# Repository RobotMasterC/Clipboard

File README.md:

# Clipboard
A TKL Keyboard that has expansion slots on both sides for extras

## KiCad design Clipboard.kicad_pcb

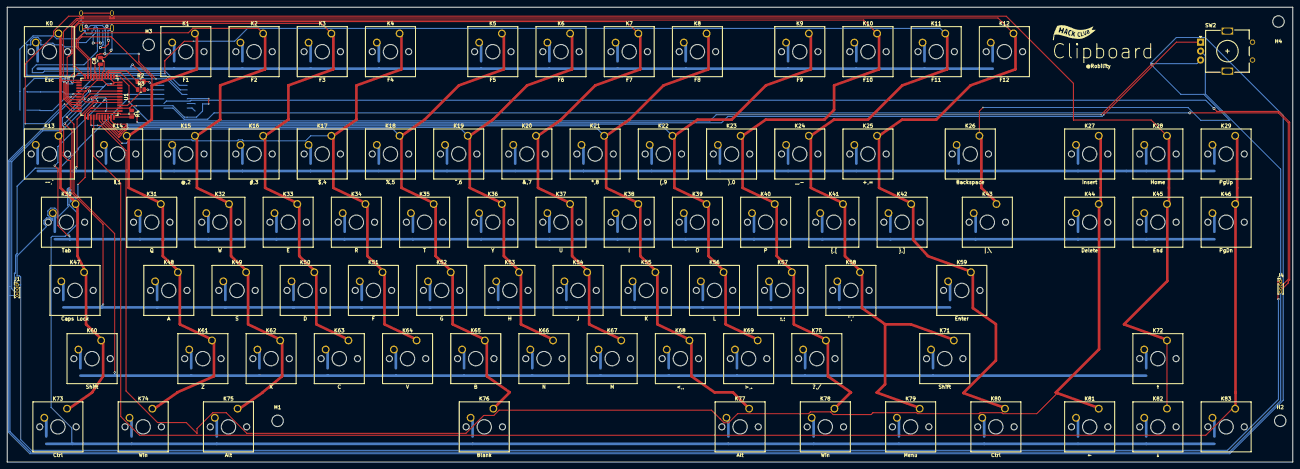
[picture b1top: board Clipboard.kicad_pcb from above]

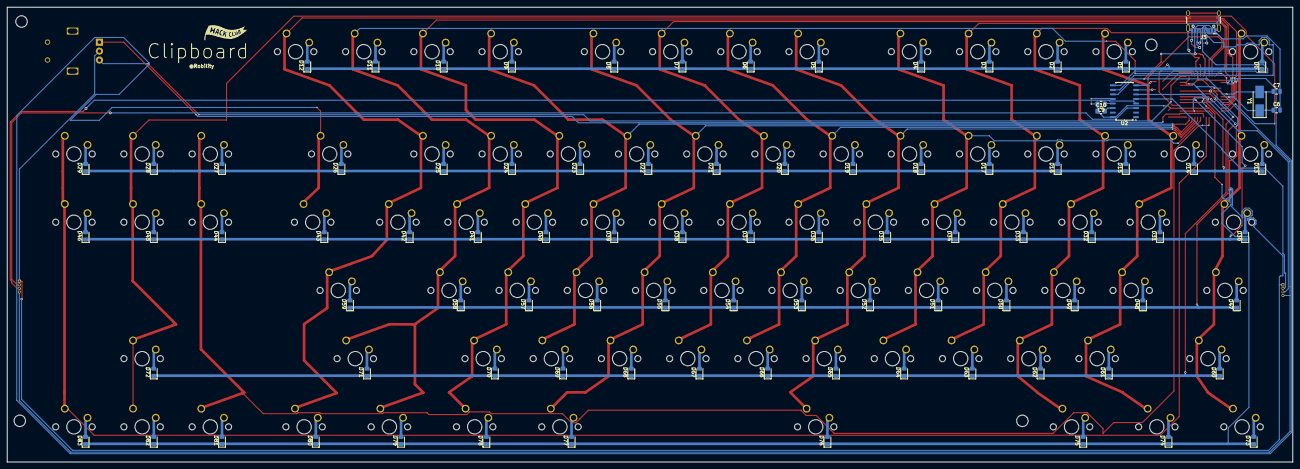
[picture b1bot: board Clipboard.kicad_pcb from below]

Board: 2 copper layers, 359.0 x 127.0 mm, 187 parts (91 on the bottom side), 128 nets.

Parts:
C6, C7: 22p; C_0805_2012Metric
C8: 1u; C_0805_2012Metric
C9, C10: 10uF; C_0805_2012Metric_Pad1.18x1.45mm_HandSolder
D0, D1, D2, D3, D4, D5, D6, D7, D8, D9, D10, D11, D12, D13, D14, D15, D16, D17, D18, D19, D20, D21, D22, D23, D24, D25, D26, D27, D28, D29, D30, D31, D32, D33, D34, D35, D36, D37, D38, D39, D40, D41, D42, D43, D44, D45, D46, D47, D48, D49, D50, D51, D52, D53, D54, D55, D56, D57, D58, D59, D60, D61, D62, D63, D64, D65, D66, D67, D68, D69, D70, D71, D72, D73, D74, D75, D76, D77, D78, D79, D80, D81, D82, D83: D; D_0805_2012Metric_Pad1.15x1.40mm_HandSolder
H1, H2, H3, H4: MountingHole; MountingHole_3.2mm_M3_DIN965
J1, J4: Conn_01x04_Socket; PinHeader_1x04_P1.00mm_Vertical
J3: USB_C_Receptacle_USB2.0_16P; USB_C_Receptacle_HCTL_HC-TYPE-C-16P-01A
K0: Esc; SW_Cherry_MX_1.00u_PCB
K1: F1; SW_Cherry_MX_1.00u_PCB
K2: F2; SW_Cherry_MX_1.00u_PCB
K3: F3; SW_Cherry_MX_1.00u_PCB
K4: F4; SW_Cherry_MX_1.00u_PCB
K5: F5; SW_Cherry_MX_1.00u_PCB
K6: F6; SW_Cherry_MX_1.00u_PCB
K7: F7; SW_Cherry_MX_1.00u_PCB
K8: F8; SW_Cherry_MX_1.00u_PCB
K9: F9; SW_Cherry_MX_1.00u_PCB
K10: F10; SW_Cherry_MX_1.00u_PCB
K11: F11; SW_Cherry_MX_1.00u_PCB
K12: F12; SW_Cherry_MX_1.00u_PCB
K13: ~~,`; SW_Cherry_MX_1.00u_PCB
K14: !,1; SW_Cherry_MX_1.00u_PCB
K15: @,2; SW_Cherry_MX_1.00u_PCB
K16: #,3; SW_Cherry_MX_1.00u_PCB
K17: $,4; SW_Cherry_MX_1.00u_PCB
K18: %,5; SW_Cherry_MX_1.00u_PCB
K19: ^,6; SW_Cherry_MX_1.00u_PCB
K20: &,7; SW_Cherry_MX_1.00u_PCB
K21: *,8; SW_Cherry_MX_1.00u_PCB
K22: (,9; SW_Cherry_MX_1.00u_PCB
K23: ),0; SW_Cherry_MX_1.00u_PCB
K24: _,-; SW_Cherry_MX_1.00u_PCB
K25: +,=; SW_Cherry_MX_1.00u_PCB
K26: Backspace; SW_Cherry_MX_2.00u_PCB
K27: Insert; SW_Cherry_MX_1.00u_PCB
K28: Home; SW_Cherry_MX_1.00u_PCB
K29: PgUp; SW_Cherry_MX_1.00u_PCB
K30: Tab; SW_Cherry_MX_1.50u_PCB
K31: Q; SW_Cherry_MX_1.00u_PCB
K32: W; SW_Cherry_MX_1.00u_PCB
K33: E; SW_Cherry_MX_1.00u_PCB
K34: R; SW_Cherry_MX_1.00u_PCB
K35: T; SW_Cherry_MX_1.00u_PCB
K36: Y; SW_Cherry_MX_1.00u_PCB
K37: U; SW_Cherry_MX_1.00u_PCB
K38: I; SW_Cherry_MX_1.00u_PCB
K39: O; SW_Cherry_MX_1.00u_PCB
K40: P; SW_Cherry_MX_1.00u_PCB
K41: {,[; SW_Cherry_MX_1.00u_PCB
K42: },]; SW_Cherry_MX_1.00u_PCB
K43: |,\; SW_Cherry_MX_1.50u_PCB
K44: Delete; SW_Cherry_MX_1.00u_PCB
K45: End; SW_Cherry_MX_1.00u_PCB
K46: PgDn; SW_Cherry_MX_1.00u_PCB
K47: Caps Lock; SW_Cherry_MX_1.75u_PCB
K48: A; SW_Cherry_MX_1.00u_PCB
K49: S; SW_Cherry_MX_1.00u_PCB
K50: D; SW_Cherry_MX_1.00u_PCB
K51: F; SW_Cherry_MX_1.00u_PCB
K52: G; SW_Cherry_MX_1.00u_PCB
K53: H; SW_Cherry_MX_1.00u_PCB
K54: J; SW_Cherry_MX_1.00u_PCB
K55: K; SW_Cherry_MX_1.00u_PCB
K56: L; SW_Cherry_MX_1.00u_PCB
K57: :,;; SW_Cherry_MX_1.00u_PCB
K58: ",'; SW_Cherry_MX_1.00u_PCB
K59: Enter; SW_Cherry_MX_2.25u_PCB
K60: Shift; SW_Cherry_MX_2.25u_PCB
K61: Z; SW_Cherry_MX_1.00u_PCB
K62: X; SW_Cherry_MX_1.00u_PCB
K63: C; SW_Cherry_MX_1.00u_PCB
K64: V; SW_Cherry_MX_1.00u_PCB
K65: B; SW_Cherry_MX_1.00u_PCB
K66: N; SW_Cherry_MX_1.00u_PCB
K67: M; SW_Cherry_MX_1.00u_PCB
K68: <,,; SW_Cherry_MX_1.00u_PCB
K69: >,.; SW_Cherry_MX_1.00u_PCB
K70: ?,/; SW_Cherry_MX_1.00u_PCB
K71: Shift; SW_Cherry_MX_2.75u_PCB
K72: ↑; SW_Cherry_MX_1.00u_PCB
K73, K80: Ctrl; SW_Cherry_MX_1.25u_PCB
K74, K78: Win; SW_Cherry_MX_1.25u_PCB
K75, K77: Alt; SW_Cherry_MX_1.25u_PCB
K76: Blank; SW_Cherry_MX_6.25u_PCB
K79: Menu; SW_Cherry_MX_1.25u_PCB
K81: ←; SW_Cherry_MX_1.00u_PCB
K82: ↓; SW_Cherry_MX_1.00u_PCB
K83: →; SW_Cherry_MX_1.00u_PCB
R2, R3: 22R; R_0805_2012Metric
R4: 10k; R_0805_2012Metric
SW2: RotaryEncoder; RotaryEncoder_Alps_EC11E_Vertical_H20mm
U1: ATmega32U4-A; TQFP-44_10x10mm_P0.8mm
U2: SL2.1A; SOIC-16_4.55x10.3mm_P1.27mm
Y1: Crystal; Crystal_SMD_5032-2Pin_5.0x3.2mm_HandSoldering

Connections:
/1D+: R2.2, U2.8 (DP1)
/1D-: R3.2, U2.7 (DM1)
/2D+: J1.3, U2.6 (DP2)
/2D-: J1.2, U2.5 (DM2)
/3D+: J4.3, U2.4 (DP3)
/3D-: J4.2, U2.3 (DM3)
/Col_0: K0.1, K13.1, K30.1, K47.1, K60.1, K73.1, U1.8 (PB0)
/Col_1: K1.1, K14.1, K31.1, K48.1, K61.1, K74.1, U1.9 (PB1)
/Col_2: K2.1, K15.1, K32.1, K49.1, K62.1, K75.1, U1.10 (PB2)
/Col_3: K3.1, K16.1, K33.1, K50.1, K63.1, U1.11 (PB3)
/Col_4: K4.1, K17.1, K34.1, K51.1, K64.1, U1.28 (PB4)
/Col_5: K5.1, K18.1, K35.1, K52.1, K65.1, K76.1, U1.29 (PB5)
/Col_6: K6.1, K19.1, K36.1, K53.1, K66.1, U1.30 (PB6)
/Col_7: K7.1, K20.1, K37.1, K54.1, K67.1, U1.12 (PB7)
/Col_8: K8.1, K21.1, K38.1, K55.1, K68.1, K77.1, U1.31 (PC6)
/Col_9: K9.1, K22.1, K39.1, K56.1, K69.1, U1.32 (PC7)
/Col_10: K10.1, K23.1, K40.1, K57.1, K70.1, K78.1, U1.18 (PD0)
/Col_11: K11.1, K24.1, K41.1, K58.1, K71.1, K79.1, U1.19 (PD1)
/Col_12: K12.1, K25.1, K42.1, K59.1, K80.1, U1.20 (PD2)
/Col_13: K26.1, K43.1, U1.21 (PD3)
/Col_14: K27.1, K44.1, K81.1, U1.25 (PD4)
/Col_15: K28.1, K45.1, K72.1, K82.1, U1.22 (PD5)
/Col_16: K29.1, K46.1, K83.1, U1.26 (PD6)
/D+: J3.A6 (D+), J3.B6 (D+), U2.10 (UDP)
/D-: J3.A7 (D-), J3.B7 (D-), U2.9 (UDM)
/Pin_A: SW2.A, U1.27 (PD7)
/Pin_B: SW2.B, U1.1 (PE6)
/Row_0: D0.1 (K), D1.1 (K), D2.1 (K), D3.1 (K), D4.1 (K), D5.1 (K), D6.1 (K), D7.1 (K), D8.1 (K), D9.1 (K), D10.1 (K), D11.1 (K), D12.1 (K), U1.36 (PF7)
/Row_1: D13.1 (K), D14.1 (K), D15.1 (K), D16.1 (K), D17.1 (K), D18.1 (K), D19.1 (K), D20.1 (K), D21.1 (K), D22.1 (K), D23.1 (K), D24.1 (K), D25.1 (K), D26.1 (K), D27.1 (K), D28.1 (K), D29.1 (K), U1.37 (PF6)
/Row_2: D30.1 (K), D31.1 (K), D32.1 (K), D33.1 (K), D34.1 (K), D35.1 (K), D36.1 (K), D37.1 (K), D38.1 (K), D39.1 (K), D40.1 (K), D41.1 (K), D42.1 (K), D43.1 (K), D44.1 (K), D45.1 (K), D46.1 (K), U1.38 (PF5)
/Row_3: D47.1 (K), D48.1 (K), D49.1 (K), D50.1 (K), D51.1 (K), D52.1 (K), D53.1 (K), D54.1 (K), D55.1 (K), D56.1 (K), D57.1 (K), D58.1 (K), D59.1 (K), U1.39 (PF4)
/Row_4: D60.1 (K), D61.1 (K), D62.1 (K), D63.1 (K), D64.1 (K), D65.1 (K), D66.1 (K), D67.1 (K), D68.1 (K), D69.1 (K), D70.1 (K), D71.1 (K), D72.1 (K), U1.40 (PF1)
/Row_5: D73.1 (K), D74.1 (K), D75.1 (K), D76.1 (K), D77.1 (K), D78.1 (K), D79.1 (K), D80.1 (K), D81.1 (K), D82.1 (K), D83.1 (K), U1.41 (PF0)
GND: C6.2, C7.2, C8.2, C9.2, C10.1, J1.1, J3.A1 (GND), J3.A5 (CC1), J3.A12 (GND), J3.B1 (GND), J3.B5 (CC2), J3.B12 (GND), J3.S1 (SHIELD), J4.1, R4.1, SW2.C, U1.5 (UGND), U1.15 (GND), U1.23 (GND), U1.35 (GND), U1.43 (GND), U2.12 (GND), U2.16 (XIN)
unnamed: D0.2 (A), K0.2
unnamed: D1.2 (A), K1.2
unnamed: D2.2 (A), K2.2
unnamed: D3.2 (A), K3.2
unnamed: D4.2 (A), K4.2
unnamed: D5.2 (A), K5.2
unnamed: D6.2 (A), K6.2
unnamed: D7.2 (A), K7.2
unnamed: D8.2 (A), K8.2
unnamed: D9.2 (A), K9.2
unnamed: D10.2 (A), K10.2
unnamed: D11.2 (A), K11.2
unnamed: D12.2 (A), K12.2
unnamed: D13.2 (A), K13.2
unnamed: D14.2 (A), K14.2
unnamed: D15.2 (A), K15.2
unnamed: D16.2 (A), K16.2
unnamed: D17.2 (A), K17.2
unnamed: D18.2 (A), K18.2
unnamed: D19.2 (A), K19.2
unnamed: D20.2 (A), K20.2
unnamed: D21.2 (A), K21.2
unnamed: D22.2 (A), K22.2
unnamed: D23.2 (A), K23.2
unnamed: D24.2 (A), K24.2
unnamed: D25.2 (A), K25.2
unnamed: D26.2 (A), K26.2
unnamed: D27.2 (A), K27.2
unnamed: D28.2 (A), K28.2
unnamed: D29.2 (A), K29.2
unnamed: D30.2 (A), K30.2
unnamed: D31.2 (A), K31.2
unnamed: D32.2 (A), K32.2
unnamed: D33.2 (A), K33.2
unnamed: D34.2 (A), K34.2
unnamed: D35.2 (A), K35.2
unnamed: D36.2 (A), K36.2
unnamed: D37.2 (A), K37.2
unnamed: D38.2 (A), K38.2
unnamed: D39.2 (A), K39.2
unnamed: D40.2 (A), K40.2
unnamed: D41.2 (A), K41.2
unnamed: D42.2 (A), K42.2
unnamed: D43.2 (A), K43.2
unnamed: D44.2 (A), K44.2
unnamed: D45.2 (A), K45.2
unnamed: D46.2 (A), K46.2
unnamed: D47.2 (A), K47.2
unnamed: D48.2 (A), K48.2
unnamed: D49.2 (A), K49.2
unnamed: D50.2 (A), K50.2
unnamed: D51.2 (A), K51.2
unnamed: D52.2 (A), K52.2
unnamed: D53.2 (A), K53.2
unnamed: D54.2 (A), K54.2
unnamed: D55.2 (A), K55.2
unnamed: D56.2 (A), K56.2
unnamed: D57.2 (A), K57.2
unnamed: D58.2 (A), K58.2
unnamed: D59.2 (A), K59.2
unnamed: D60.2 (A), K60.2
unnamed: D61.2 (A), K61.2
unnamed: D62.2 (A), K62.2
unnamed: D63.2 (A), K63.2
unnamed: D64.2 (A), K64.2
unnamed: D65.2 (A), K65.2
unnamed: D66.2 (A), K66.2
unnamed: D67.2 (A), K67.2
unnamed: D68.2 (A), K68.2
unnamed: D69.2 (A), K69.2
unnamed: D70.2 (A), K70.2
unnamed: D71.2 (A), K71.2
unnamed: D72.2 (A), K72.2
unnamed: D73.2 (A), K73.2
unnamed: D74.2 (A), K74.2
unnamed: D75.2 (A), K75.2
unnamed: D76.2 (A), K76.2
unnamed: D77.2 (A), K77.2
unnamed: D78.2 (A), K78.2
unnamed: D79.2 (A), K79.2
unnamed: D80.2 (A), K80.2
unnamed: D81.2 (A), K81.2
unnamed: D82.2 (A), K82.2
unnamed: D83.2 (A), K83.2
unnamed: R2.1, U1.4 (D+)
unnamed: R3.1, U1.3 (D-)
unnamed: C8.1, U1.6 (UCAP)
unnamed: C6.1, U1.17 (XTAL1), Y1.1
unnamed: C7.1, U1.16 (XTAL2), Y1.2
unnamed: R4.2, U1.33 (~HWB/PE2)
unnamed: C9.1, U2.13 (VDD3)
unnamed: C10.2, U2.14 (VDD18)
VBUS: J1.4, J3.A4 (VBUS), J3.A9 (VBUS), J3.B4 (VBUS), J3.B9 (VBUS), J4.4, U1.7 (VBUS), U2.11 (VCC5V)
VCC: U1.2 (UVCC), U1.14 (VCC), U1.24 (AVCC), U1.34 (VCC), U1.44 (AVCC)

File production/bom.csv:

Designator,Footprint,Quantity,Value,LCSC Part #
"C10, C9",0805,2,10uF,
"C6, C7",0805,2,22p,
C8,0805,1,1u,
"D0, D1, D10, D11, D12, D13, D14, D15, D16, D17, D18, D19, D2, D20, D21, D22, D23, D24, D25, D26, D27, D28, D29, D3, D30, D31, D32, D33, D34, D35, D36, D37, D38, D39, D4, D40, D41, D42, D43, D44, D45, D46, D47, D48, D49, D5, D50, D51, D52, D53, D54, D55, D56, D57, D58, D59, D6, D60, D61, D62, D63, D64, D65, D66, D67, D68, D69, D7, D70, D71, D72, D73, D74, D75, D76, D77, D78, D79, D8, D80, D81, D82, D83, D9",0805,84,D,
"H1, H2, H3, H4",MountingHole_3.2mm_M3_DIN965,4,MountingHole,
"J1, J4",PinHeader_1x04_P1.00mm_Vertical,2,Conn_01x04_Socket,
J3,USB_C_Receptacle_HCTL_HC-TYPE-C-16P-01A,1,USB_C_Receptacle_USB2.0_16P,
K0,SW_Cherry_MX_1.00u_PCB,1,Esc,
K1,SW_Cherry_MX_1.00u_PCB,1,F1,
K10,SW_Cherry_MX_1.00u_PCB,1,F10,
K11,SW_Cherry_MX_1.00u_PCB,1,F11,
K12,SW_Cherry_MX_1.00u_PCB,1,F12,
K13,SW_Cherry_MX_1.00u_PCB,1,"~~,`",
K14,SW_Cherry_MX_1.00u_PCB,1,"!,1",
K15,SW_Cherry_MX_1.00u_PCB,1,"@,2",
K16,SW_Cherry_MX_1.00u_PCB,1,"#,3",
K17,SW_Cherry_MX_1.00u_PCB,1,"$,4",
K18,SW_Cherry_MX_1.00u_PCB,1,"%,5",
K19,SW_Cherry_MX_1.00u_PCB,1,"^,6",
K2,SW_Cherry_MX_1.00u_PCB,1,F2,
K20,SW_Cherry_MX_1.00u_PCB,1,"&,7",
K21,SW_Cherry_MX_1.00u_PCB,1,"*,8",
K22,SW_Cherry_MX_1.00u_PCB,1,"(,9",
K23,SW_Cherry_MX_1.00u_PCB,1,"),0",
K24,SW_Cherry_MX_1.00u_PCB,1,"_,-",
K25,SW_Cherry_MX_1.00u_PCB,1,"+,=",
K26,SW_Cherry_MX_2.00u_PCB,1,Backspace,
K27,SW_Cherry_MX_1.00u_PCB,1,Insert,
K28,SW_Cherry_MX_1.00u_PCB,1,Home,
K29,SW_Cherry_MX_1.00u_PCB,1,PgUp,
K3,SW_Cherry_MX_1.00u_PCB,1,F3,
K30,SW_Cherry_MX_1.50u_PCB,1,Tab,
K31,SW_Cherry_MX_1.00u_PCB,1,Q,
K32,SW_Cherry_MX_1.00u_PCB,1,W,
K33,SW_Cherry_MX_1.00u_PCB,1,E,
K34,SW_Cherry_MX_1.00u_PCB,1,R,
K35,SW_Cherry_MX_1.00u_PCB,1,T,
K36,SW_Cherry_MX_1.00u_PCB,1,Y,
K37,SW_Cherry_MX_1.00u_PCB,1,U,
K38,SW_Cherry_MX_1.00u_PCB,1,I,
K39,SW_Cherry_MX_1.00u_PCB,1,O,
K4,SW_Cherry_MX_1.00u_PCB,1,F4,
K40,SW_Cherry_MX_1.00u_PCB,1,P,
K41,SW_Cherry_MX_1.00u_PCB,1,"{,[",
K42,SW_Cherry_MX_1.00u_PCB,1,"},]",
K43,SW_Cherry_MX_1.50u_PCB,1,"|,\",
K44,SW_Cherry_MX_1.00u_PCB,1,Delete,
K45,SW_Cherry_MX_1.00u_PCB,1,End,
K46,SW_Cherry_MX_1.00u_PCB,1,PgDn,
K47,SW_Cherry_MX_1.75u_PCB,1,Caps Lock,
K48,SW_Cherry_MX_1.00u_PCB,1,A,
K49,SW_Cherry_MX_1.00u_PCB,1,S,
K5,SW_Cherry_MX_1.00u_PCB,1,F5,
K50,SW_Cherry_MX_1.00u_PCB,1,D,
K51,SW_Cherry_MX_1.00u_PCB,1,F,
K52,SW_Cherry_MX_1.00u_PCB,1,G,
K53,SW_Cherry_MX_1.00u_PCB,1,H,
K54,SW_Cherry_MX_1.00u_PCB,1,J,
K55,SW_Cherry_MX_1.00u_PCB,1,K,
K56,SW_Cherry_MX_1.00u_PCB,1,L,
K57,SW_Cherry_MX_1.00u_PCB,1,":,;",
K58,SW_Cherry_MX_1.00u_PCB,1,""",'",
K59,SW_Cherry_MX_2.25u_PCB,1,Enter,
K6,SW_Cherry_MX_1.00u_PCB,1,F6,
K60,SW_Cherry_MX_2.25u_PCB,1,Shift,
K61,SW_Cherry_MX_1.00u_PCB,1,Z,
K62,SW_Cherry_MX_1.00u_PCB,1,X,
K63,SW_Cherry_MX_1.00u_PCB,1,C,
K64,SW_Cherry_MX_1.00u_PCB,1,V,
K65,SW_Cherry_MX_1.00u_PCB,1,B,
K66,SW_Cherry_MX_1.00u_PCB,1,N,
K67,SW_Cherry_MX_1.00u_PCB,1,M,
K68,SW_Cherry_MX_1.00u_PCB,1,"<,,",
K69,SW_Cherry_MX_1.00u_PCB,1,">,.",
K7,SW_Cherry_MX_1.00u_PCB,1,F7,
K70,SW_Cherry_MX_1.00u_PCB,1,"?,/",
K71,SW_Cherry_MX_2.75u_PCB,1,Shift,
K72,SW_Cherry_MX_1.00u_PCB,1,↑,
"K73, K80",SW_Cherry_MX_1.25u_PCB,2,Ctrl,
"K74, K78",SW_Cherry_MX_1.25u_PCB,2,Win,
"K75, K77",SW_Cherry_MX_1.25u_PCB,2,Alt,
K76,SW_Cherry_MX_6.25u_PCB,1,Blank,
K79,SW_Cherry_MX_1.25u_PCB,1,Menu,
K8,SW_Cherry_MX_1.00u_PCB,1,F8,
K81,SW_Cherry_MX_1.00u_PCB,1,←,
K82,SW_Cherry_MX_1.00u_PCB,1,↓,
K83,SW_Cherry_MX_1.00u_PCB,1,→,
K9,SW_Cherry_MX_1.00u_PCB,1,F9,
"R2, R3",0805,2,22R,
R4,0805,1,10k,
SW2,RotaryEncoder_Alps_EC11E_Vertical_H20mm,1,RotaryEncoder,
U1,TQFP-44_10x10mm_P0.8mm,1,ATmega32U4-A,
U2,SOIC-16_4.55x10.3mm_P1.27mm,1,SL2.1A,
Y1,Crystal_SMD_5032-2Pin_5.0x3.2mm_HandSoldering,1,Crystal,
